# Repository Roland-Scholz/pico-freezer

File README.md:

# pico-freezer
Remake of the Turbo-Freezer 2005/11

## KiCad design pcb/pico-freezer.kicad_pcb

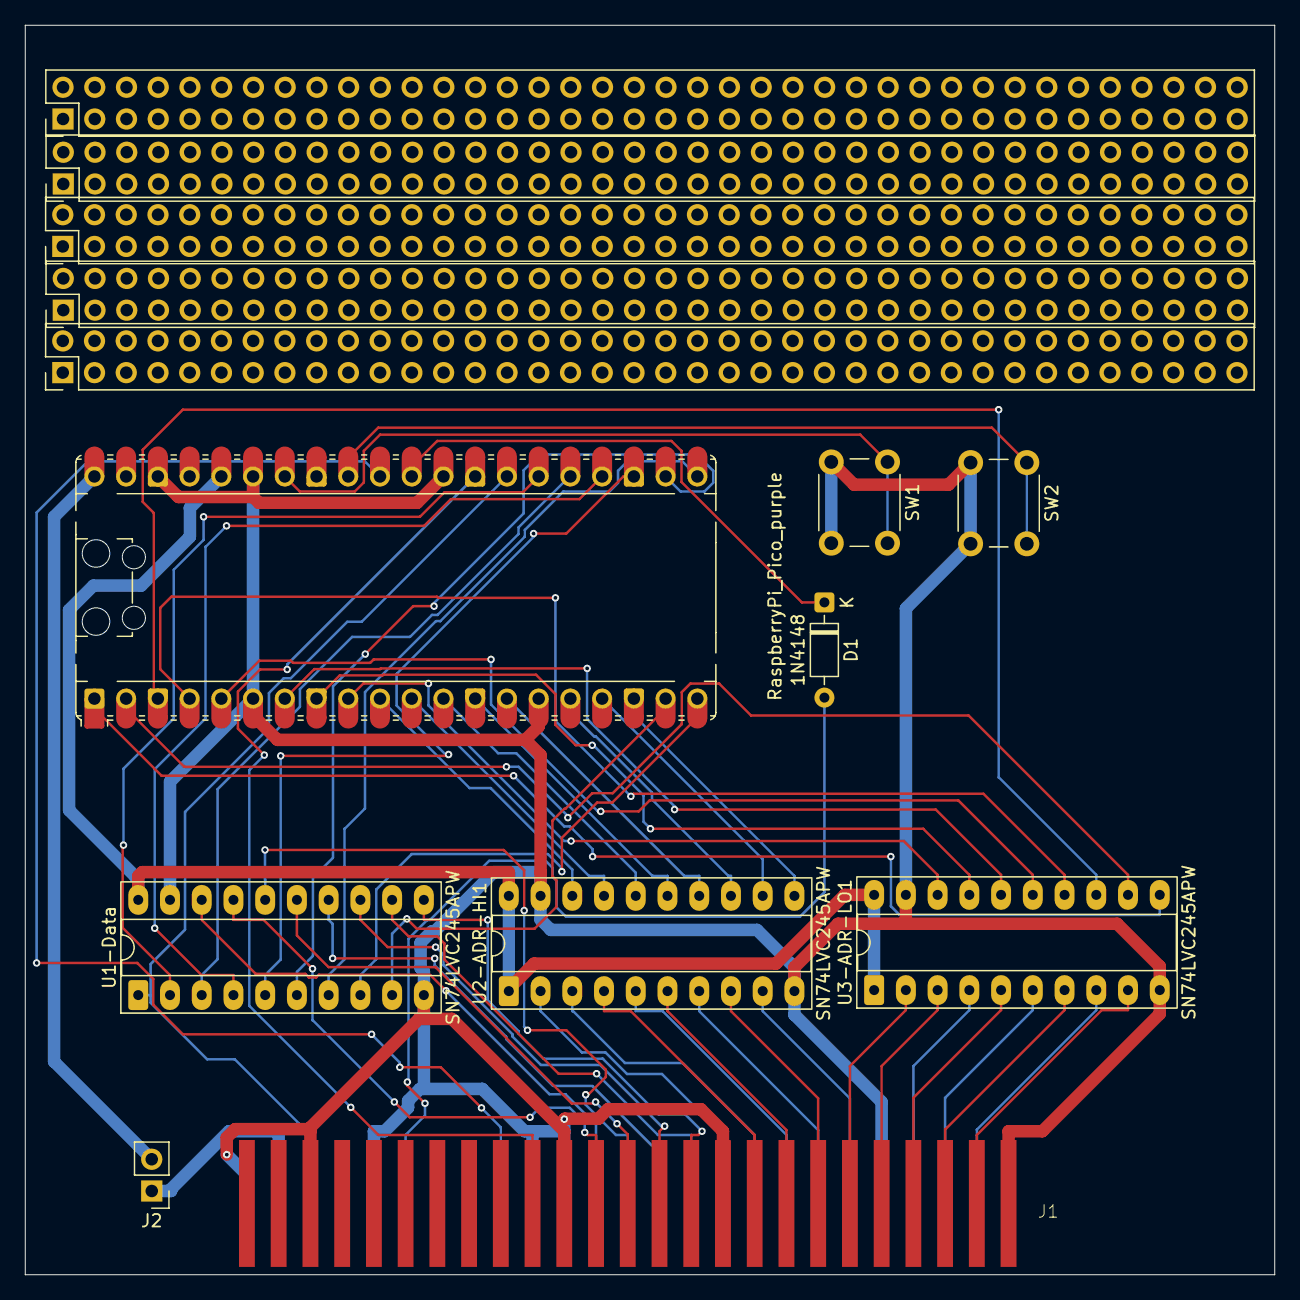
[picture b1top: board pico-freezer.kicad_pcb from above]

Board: 2 copper layers, 100.0 x 100.0 mm, 9 parts (0 on the bottom side), 59 nets.

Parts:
A1: RaspberryPi_Pico_purple; RaspberryPi_Pico_Common_Unspecified
D1: 1N4148; D_DO-35_SOD27_P7.62mm_Horizontal
J1: PARALLEL_BUS_EDGE; PARALLEL_BUS_INTERFACE_DEVICE
J2: Conn_01x02; PinHeader_1x02_P2.54mm_Vertical
SW1, SW2: SW_Push; SW_PUSH_6mm
U1-Data, U2-ADR-HI1, U3-ADR-LO1: SN74LVC245APW; DIP-20_W7.62mm_Socket_LongPads

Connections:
+3V3: A1.36 (3V3), U1-Data.20 (VCC), U2-ADR-HI1.1 (DIR), U2-ADR-HI1.20 (VCC), U3-ADR-LO1.1 (DIR), U3-ADR-LO1.20 (VCC)
+5V: J1.48 (RESERVED4), J2.1
A0: J1.3 (A0), U3-ADR-LO1.9 (A8)
A0P: A1.1 (GPIO0), U3-ADR-LO1.11 (B8)
A1: J1.4 (A1), U3-ADR-LO1.8 (A7)
A1P: A1.2 (GPIO1), U3-ADR-LO1.12 (B7)
A2: J1.5 (A2), U3-ADR-LO1.7 (A6)
A2P: A1.3 (GPIO2), U3-ADR-LO1.13 (B6)
A3: J1.6 (A3), U3-ADR-LO1.6 (A5)
A3P: A1.4 (GPIO3), U3-ADR-LO1.14 (B5)
A4: J1.7 (A4), U3-ADR-LO1.5 (A4)
A4P: A1.5 (GPIO4), U3-ADR-LO1.15 (B4)
A5: J1.8 (A5), U3-ADR-LO1.4 (A3)
A5P: A1.7 (GPIO5), U3-ADR-LO1.16 (B3)
A6: J1.9 (A6), U3-ADR-LO1.3 (A2)
A6P: A1.8 (GPIO6), U3-ADR-LO1.17 (B2)
A7: J1.11 (A7), U3-ADR-LO1.2 (A1)
A7P: A1.9 (GPIO7), U3-ADR-LO1.18 (B1)
A8: J1.12 (A8), U2-ADR-HI1.9 (A8)
A8P: A1.10 (GPIO8), U2-ADR-HI1.18 (B1)
A9: J1.13 (A9), U2-ADR-HI1.8 (A7)
A9P: A1.11 (GPIO9), U2-ADR-HI1.17 (B2)
A10: J1.14 (A10), U2-ADR-HI1.7 (A6)
A10P: A1.12 (GPIO10), U2-ADR-HI1.16 (B3)
A11: J1.15 (A11), U2-ADR-HI1.6 (A5)
A11P: A1.13 (GPIO11), U2-ADR-HI1.15 (B4)
A12: J1.16 (A12), U2-ADR-HI1.5 (A4)
A12P: A1.14 (GPIO12), U2-ADR-HI1.14 (B5)
A13: J1.17 (A13), U2-ADR-HI1.4 (A3)
A13P: A1.16 (GPIO13), U2-ADR-HI1.13 (B6)
A14: J1.18 (A14), U2-ADR-HI1.3 (A2)
A14P: A1.17 (GPIO14), U2-ADR-HI1.12 (B7)
A15: J1.20 (A15), U2-ADR-HI1.2 (A1)
A15P: A1.18 (GPIO15), U2-ADR-HI1.11 (B8)
D0: J1.21 (D0), U1-Data.11 (B8)
D0P: A1.19 (GPIO16), U1-Data.9 (A8)
D1: J1.22 (D1), U1-Data.12 (B7)
D1P: A1.20 (GPIO17), U1-Data.8 (A7)
D2: J1.23 (D2), U1-Data.13 (B6)
D2P: A1.21 (GPIO18), U1-Data.7 (A6)
D3: J1.24 (D3), U1-Data.14 (B5)
D3P: A1.22 (GPIO19), U1-Data.6 (A5)
D4: J1.25 (D4), U1-Data.15 (B4)
D4P: A1.23 (GPIO20), U1-Data.5 (A4)
D5: J1.26 (D5), U1-Data.16 (B3)
D5P: A1.24 (GPIO21), U1-Data.4 (A3)
D6: J1.27 (D6), U1-Data.17 (B2)
D6P: A1.25 (GPIO22), U1-Data.3 (A2)
D7: J1.28 (D7), U1-Data.18 (B1)
D7P: A1.26 (GPIO23), U1-Data.2 (A1)
Freeze: A1.32 (GPIO28), SW2.1
GND: A1.6 (GND), A1.15 (GND), A1.29 (GND), A1.35 (GND), A1.38 (GND), J1.1 (GND), J1.10 (GND2), J1.19 (GND4), J1.29 (GND5), J1.30 (GND6), J1.32 (GND7), J1.42 (GND8), J1.45 (GND3), J1.50 (GND1), SW1.2, SW2.2, U1-Data.10 (GND), U1-Data.19 (~OE), U2-ADR-HI1.10 (GND), U2-ADR-HI1.19 (~OE), U3-ADR-LO1.10 (GND), U3-ADR-LO1.19 (~OE)
LRw: A1.27 (GPIO24), J1.46 (R/~W), U1-Data.1 (DIR)
unnamed: A1.30 (GPIO26), D1.1 (K)
PHI2: A1.28 (GPIO25), J1.31 (PHI2)
REF\: D1.2 (A), J1.40 (~REF)
RST\: A1.31 (GPIO27), J1.34 (~RST)
RUN: A1.34 (RUN), SW1.1
VBUS: A1.40 (VBUS), J2.2
